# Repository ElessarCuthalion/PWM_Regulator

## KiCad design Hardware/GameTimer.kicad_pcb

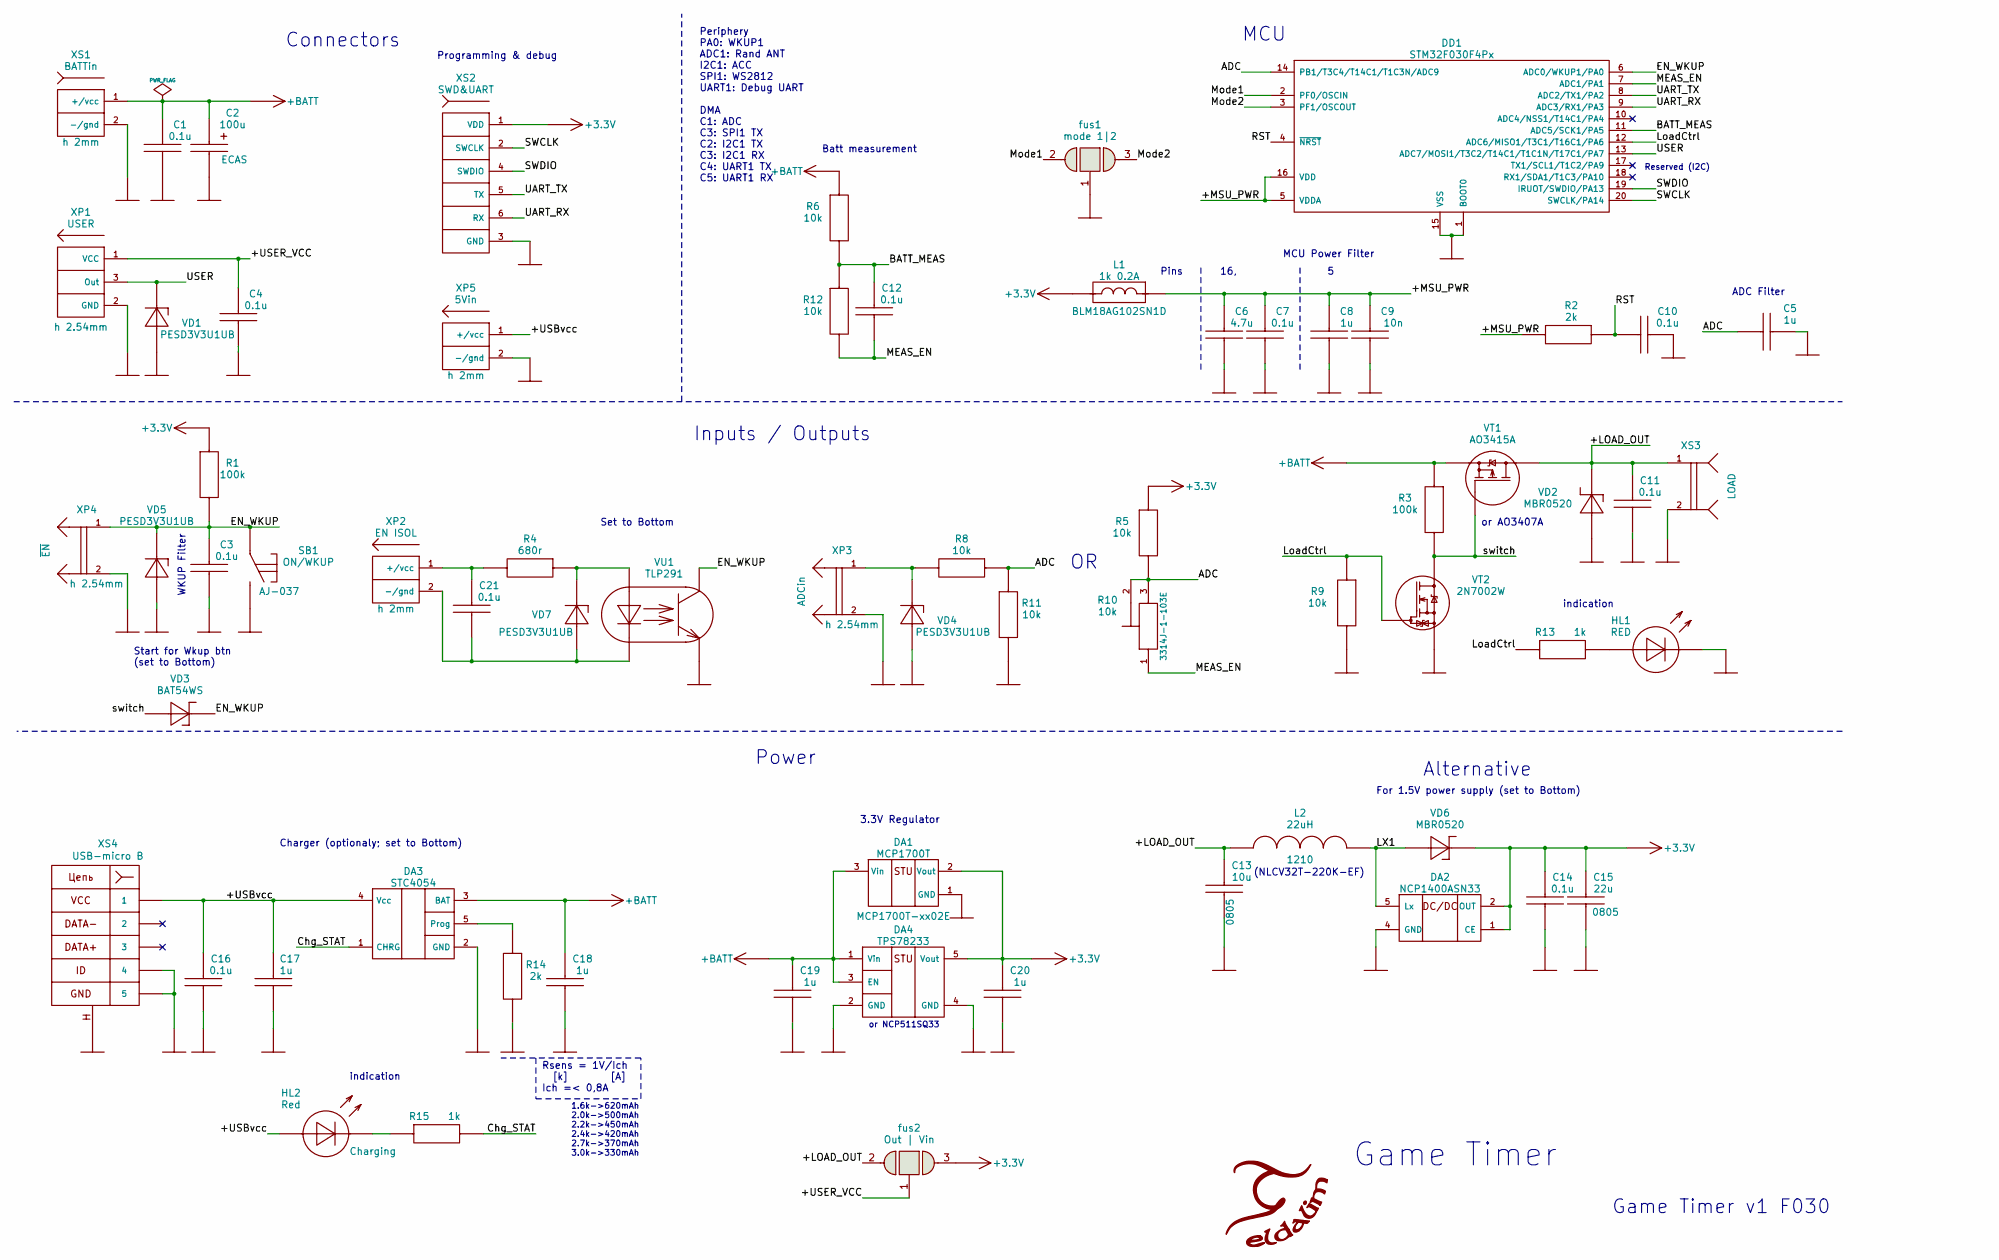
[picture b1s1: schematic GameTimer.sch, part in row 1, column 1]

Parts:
C1, C3, C4, C7, C10, C11, C12, C14, C16, C21: 0.1u; CAP0603
C2: 100u; CAP_pol_SMD-7343
C5, C8, C17, C18, C19, C20: 1u; CAP0603
C6: 4.7u; CAP0603
C9: 10n; CAP0603
C13: 10u; CAP0805
C15: 22u; CAP0805
DA1: MCP1700T; SOT23-3
DA2: NCP1400ASN33; SOT23-5
DA3: STC4054; SOT23-5
DA4: TPS78233; SOT23-5
DD1: STM32F030F4Px; TSSOP20
HL1: RED; LED0805
HL2: Red; LED0805
L1: 1k 0.2A; Bead_0603
L2: 22uH; IND1210_LQH32C
Logo1: Eldalim; Eldalim_10x8
R1, R3: 100k; RES0603
R2, R14: 2k; RES0603
R4: 680r; RES0603
R5, R6, R8, R9, R11, R12: 10k; RES0603
R10: 10k; RES_TRIM_Bourns3314J-1
R13, R15: 1k; RES0603
SB1: ON/WKUP; BTN_5x5(AJ-037)
VD1, VD4, VD5, VD7: PESD3V3U1UB; SOD523
VD2, VD6: MBR0520; SOD123
VD3: BAT54WS; SOD323
VT1: AO3415A; SOT23A
VT2: 2N7002W; SOT323
VU1: TLP291; opto_SOP4
XP1: USER; for_SENS_PLS2-3
XP2: EN ISOL; for_PolarOut_PLS2-2
XP3: ADCin; PLS2-2
XP4: ~EN; PLS2-2
XP5: 5Vin; for_PolarOut_PLS2-2
XS1: BATTin; for_PolarOut_PLS2-2
XS2: SWD&UART; for_SWD&UART_PBS-6
XS3: LOAD; PBS2-2
XS4: USB-micro B; USB-micro_B
fus1: mode 1|2; FuseSolder_x2_0603
fus2: Out | Vin; FuseSolder_x2_0603

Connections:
+3.3V: C14.1, C15.1, C20.1, DA1.2 (Vout), DA2.1 (CE), DA2.2 (OUT), DA4.5 (Vout), L1.1, R1.1, R5.1, VD6.C, XS2.1 (VDD), fus2.3
+BATT: C1.1, C2.1, C18.1, C19.1, DA1.3 (Vin), DA3.3 (BAT), DA4.1 (Vin), DA4.3 (EN), R3.1, R6.1, VT1.2 (S), XS1.1 (+/vcc)
/+LOAD_OUT: C11.1, C13.1, L2.1, VD2.C, VT1.3 (D), XS3.1, fus2.2
/+MSU_PWR: C6.1, C7.1, C8.1, C9.1, DD1.5 (VDDA), DD1.16 (VDD), L1.2, R2.2
/+USBvcc: C16.1, C17.1, DA3.4 (Vcc), HL2.A, XP5.1 (+/vcc), XS4.1
/+USER_VCC: C4.1, XP1.1 (VCC), fus2.1
/ADC: C5.1, DD1.14 (PB1/T3C4/T14C1/T1C3N/ADC9), R5.2, R8.1, R10.2, R10.3, R11.1
/BATT_MEAS: C12.1, DD1.11 (ADC5/SCK1/PA5), R6.2, R12.1
/Chg_STAT: DA3.1 (CHRG), R15.2
/EN_WKUP: C3.1, DD1.6 (ADC0/WKUP1/PA0), R1.2, SB1.1, VD3.C, VD5.C, VU1.4 (C), XP4.1
/LX1: DA2.5 (Lx), L2.2, VD6.A
/LoadCtrl: DD1.12 (ADC6/MISO1/T3C1/T16C1/PA6), R9.1, R13.1, VT2.1 (G)
/MEAS_EN: C12.2, DD1.7 (ADC1/PA1), R10.1, R12.2
/Mode1: DD1.2 (PF0/OSCIN), fus1.2
/Mode2: DD1.3 (PF1/OSCOUT), fus1.3
/RST: C10.1, DD1.4 (~NRST), R2.1
/SWCLK: DD1.20 (SWCLK/PA14), XS2.2 (SWCLK)
/SWDIO: DD1.19 (IRUOT/SWDIO/PA13), XS2.4 (SWDIO)
/UART_RX: DD1.9 (ADC3/RX1/PA3), XS2.6 (RX)
/UART_TX: DD1.8 (ADC2/TX1/PA2), XS2.5 (TX)
/USER: DD1.13 (ADC7/MOSI1/T3C2/T14C1/T1C1N/T17C1/PA7), VD1.C, XP1.3 (Out)
/switch: R3.2, VD3.A, VT1.1 (G), VT2.3 (D)
GND: C1.2, C2.2, C3.2, C4.2, C5.2, C6.2, C7.2, C8.2, C9.2, C10.2, C11.2, C13.2, C14.2, C15.2, C16.2, C17.2, C18.2, C19.2, C20.2, DA1.1 (GND), DA2.4 (GND), DA3.2 (GND), DA4.2 (GND), DA4.4 (GND), DD1.1 (BOOT0), DD1.15 (VSS), HL1.C, R9.2, R11.2, R14.2, SB1.2, VD1.A, VD2.A, VD4.A, VD5.A, VT2.2 (S), VU1.3 (E), XP1.2 (GND), XP3.2, XP4.2, XP5.2 (-/gnd), XS1.2 (-/gnd), XS2.3 (GND), XS3.2, XS4.4, XS4.5, XS4.SHLD, fus1.1
unnamed: C21.1, R4.2, XP2.1 (+/vcc)
unnamed: C21.2, VD7.A, VU1.2 (C), XP2.2 (-/gnd)
unnamed: DA3.5 (Prog), R14.1
unnamed: HL1.A, R13.2
unnamed: HL2.C, R15.1
unnamed: R4.1, VD7.C, VU1.1 (A)
unnamed: R8.2, VD4.C, XP3.1

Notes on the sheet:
Game Timer
Game Timer v1 F030
Programming & debug
Periphery PA0: WKUP1 ADC1: Rand ANT I2C1: ACC SPI1: WS2812 UART1: Debug UART DMA C1: ADC C3: SPI1 TX C2: I2C1 TX C3: I2C1 RX C4: UART1 TX C5: UART1 RX
MCU
Power
Connectors
MCU Power Filter
Pins 16, 5
indication
3.3V Regulator
Inputs / Outputs
WKUP Filter
ADC Filter
Reserved (I2C)
or AO3407A
or NCP511SQ33
Set to Bottom
Batt measurement
(NLCV32T-220K-EF)
For 1.5V power supply (set to Bottom)
Alternative
Rsens = 1V/Ich [k] [A] Ich =< 0,8A
1.6k->620mAh 2.0k->500mAh 2.2k->450mAh 2.4k->420mAh 2.7k->370mAh 3.0k->330mAh
Charger (optionaly; set to Bottom)
Start for Wkup btn (set to Bottom)

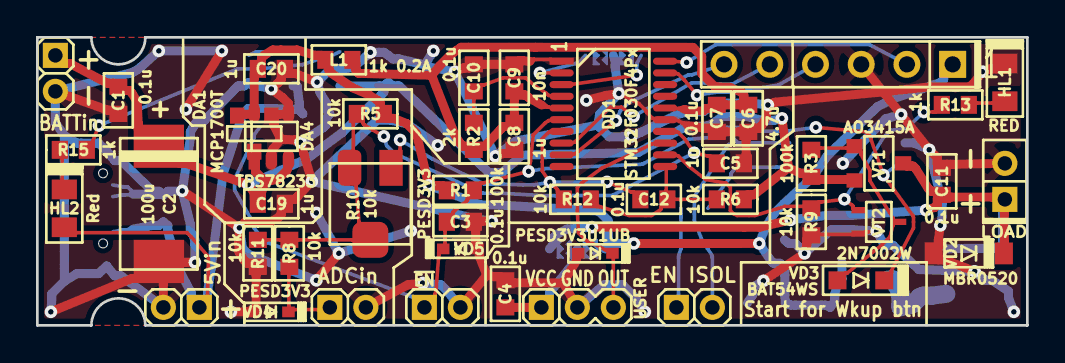
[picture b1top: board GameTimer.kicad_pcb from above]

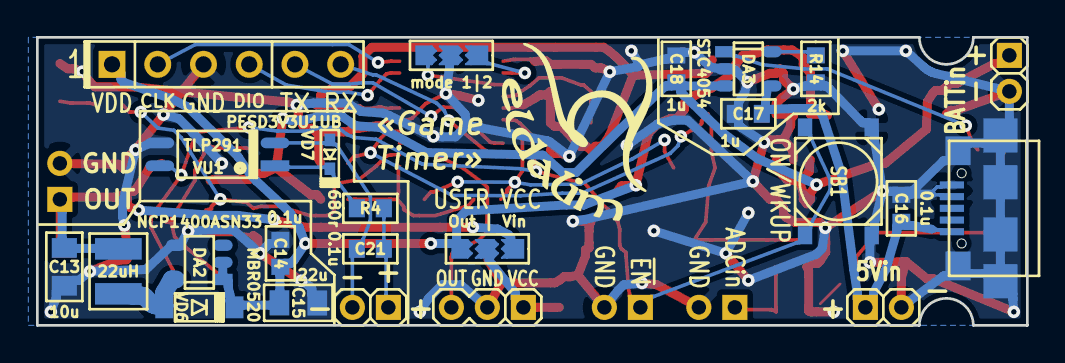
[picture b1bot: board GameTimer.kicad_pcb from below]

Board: 2 copper layers, 55.0 x 16.0 mm, 67 parts (20 on the bottom side), 30 nets.

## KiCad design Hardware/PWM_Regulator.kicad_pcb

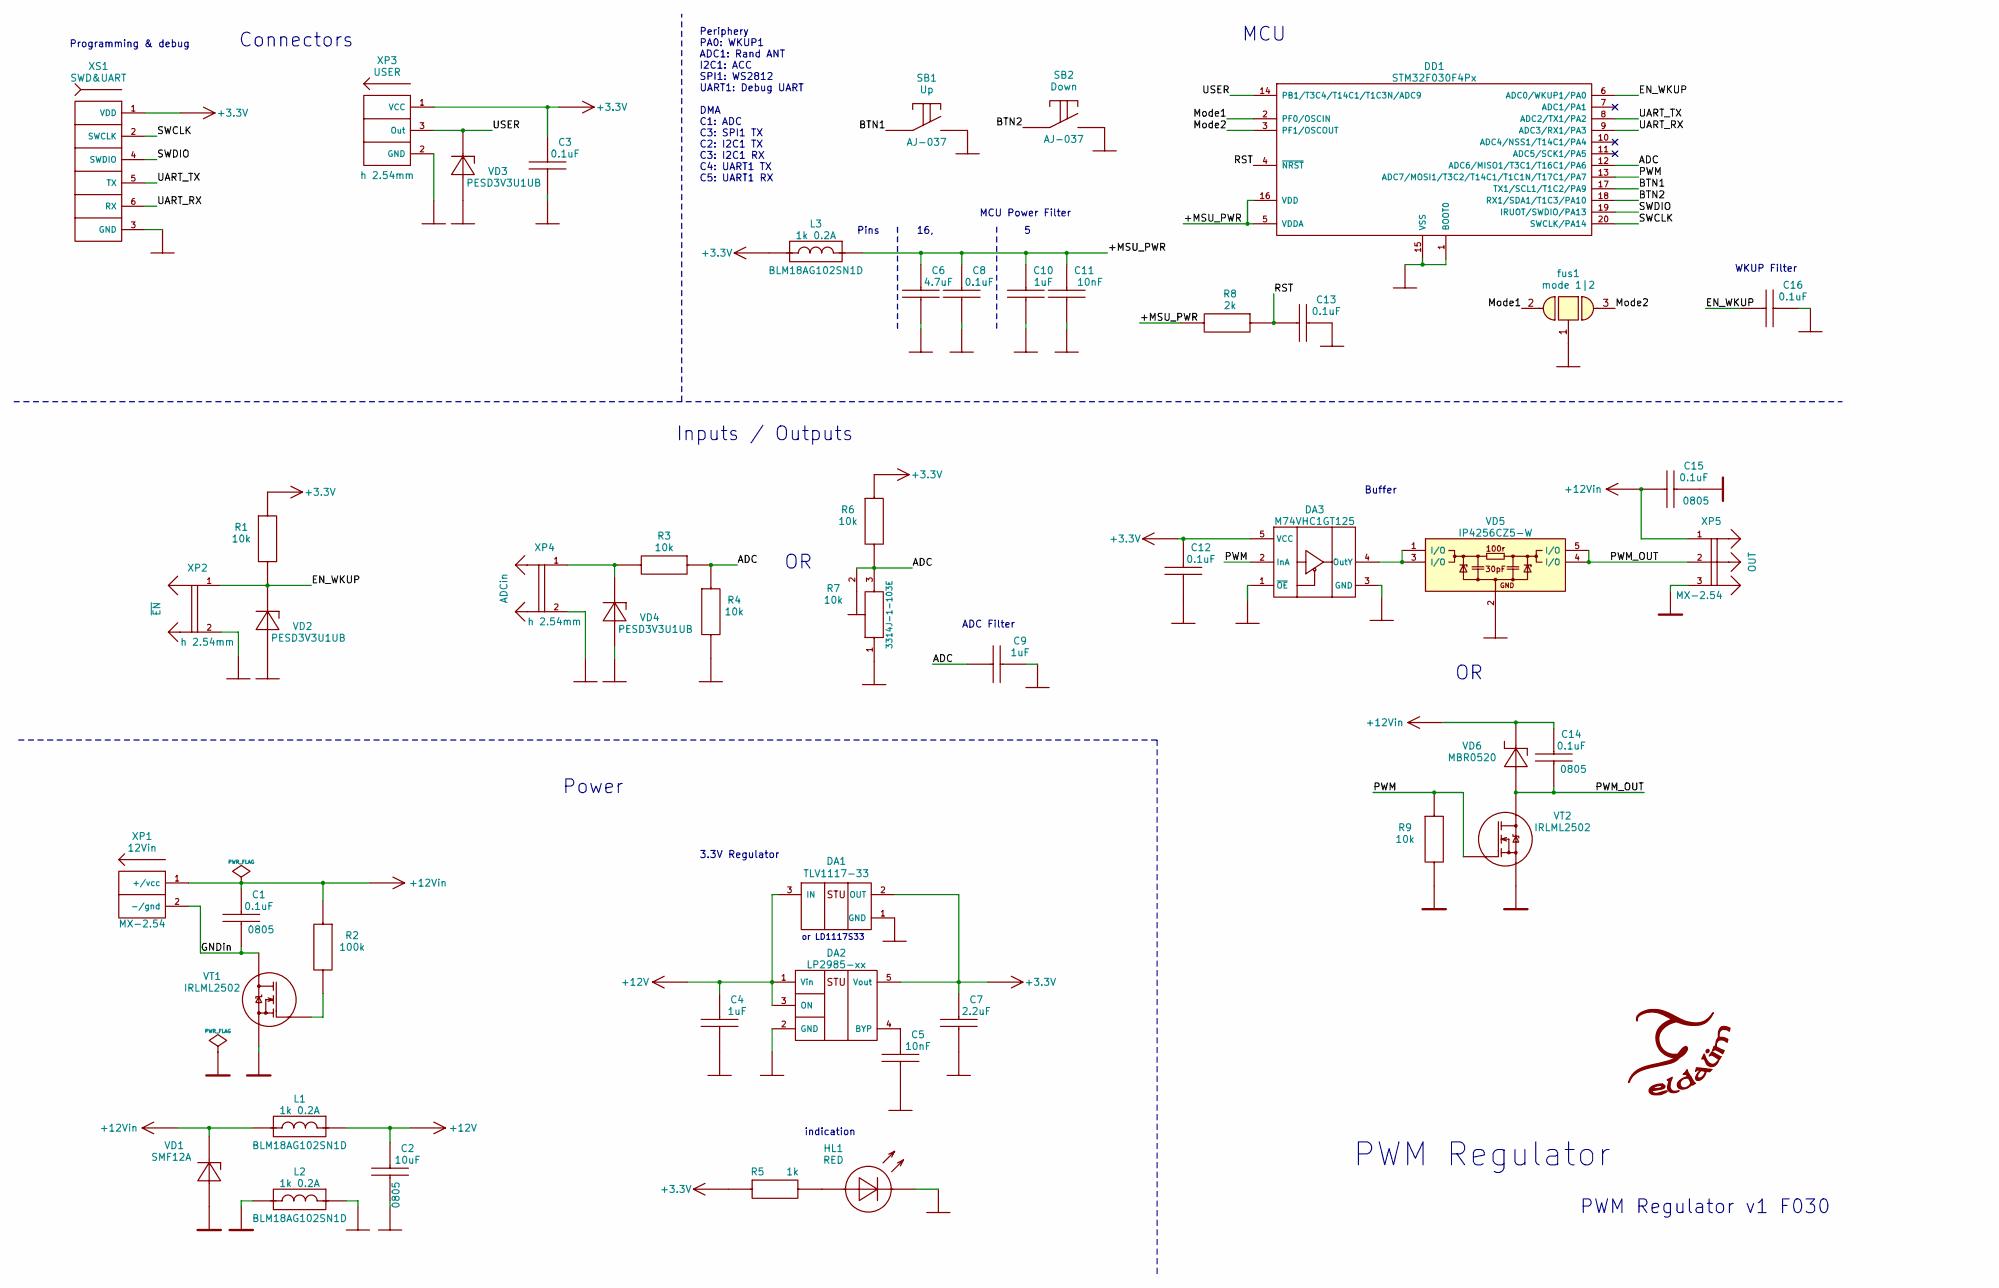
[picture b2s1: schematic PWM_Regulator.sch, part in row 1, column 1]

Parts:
C1, C14, C15: 0.1uF; CAP0805
C2: 10uF; CAP0805
C3, C8, C12, C13, C16: 0.1uF; CAP0603
C4, C9, C10: 1uF; CAP0603
C5, C11: 10nF; CAP0603
C6: 4.7uF; CAP0603
C7: 2.2uF; CAP0603
DA1: TLV1117-33; SOT223
DA2: LP2985-xx; SOT23-5
DA3: M74VHC1GT125; SOT23-5
DD1: STM32F030F4Px; TSSOP20
HL1: RED; LED0805
L1, L2, L3: 1k 0.2A; Bead_0603
Logo1: Eldalim; Eldalim_10x8
R1, R3, R4, R6, R9: 10k; RES0603
R2: 100k; RES0603
R5: 1k; RES0603
R7: 10k; RES_TRIM_Bourns3314J-1
R8: 2k; RES0603
SB1: Up; BTN_5x5(AJ-037)
SB2: Down; BTN_5x5(AJ-037)
VD1: SMF12A; SOD123
VD2, VD3, VD4: PESD3V3U1UB; SOD523
VD5: IP4256CZ5-W; SOT665
VD6: MBR0520; SOD123
VT1, VT2: IRLML2502; SOT23-3
XP1: 12Vin; for_PolarOut_MX2.54-2R
XP2: ~EN; PLS-2
XP3: USER; for_SENS_PLS-3
XP4: ADCin; PLS-2
XP5: OUT; MX2.54-3R
XS1: SWD&UART; for_SWD&UART_PBS-6
fus1: mode 1|2; FuseSolder_x2_0603

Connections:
+3.3V: C3.1, C7.1, C12.1, DA1.2 (OUT), DA2.5 (Vout), DA3.5 (VCC), L3.1, R1.1, R5.1, R6.1, XP3.1 (VCC), XS1.1 (VDD)
+12V: C2.1, C4.1, DA1.3 (IN), DA2.1 (Vin), DA2.3 (ON), L1.2
+12Vin: C1.1, C14.1, C15.1, L1.1, R2.1, VD1.C, VD6.C, XP1.1 (+/vcc), XP5.1
/+MSU_PWR: C6.1, C8.1, C10.1, C11.1, DD1.5 (VDDA), DD1.16 (VDD), L3.2, R8.2
/ADC: C9.1, DD1.12 (ADC6/MISO1/T3C1/T16C1/PA6), R3.1, R4.1, R6.2, R7.2, R7.3
/BTN1: DD1.17 (TX1/SCL1/T1C2/PA9), SB1.1
/BTN2: DD1.18 (RX1/SDA1/T1C3/PA10), SB2.1
/EN_WKUP: C16.1, DD1.6 (ADC0/WKUP1/PA0), R1.2, VD2.C, XP2.1
/GNDin: C1.2, VT1.3 (D), XP1.2 (-/gnd)
/Mode1: DD1.2 (PF0/OSCIN), fus1.2
/Mode2: DD1.3 (PF1/OSCOUT), fus1.3
/PWM: DA3.2 (InA), DD1.13 (ADC7/MOSI1/T3C2/T14C1/T1C1N/T17C1/PA7), R9.1, VT2.1 (G)
/PWM_OUT: C14.2, VD5.4 (I/O), VD5.5 (I/O), VD6.A, VT2.3 (D), XP5.2
/RST: C13.1, DD1.4 (~NRST), R8.1
/SWCLK: DD1.20 (SWCLK/PA14), XS1.2 (SWCLK)
/SWDIO: DD1.19 (IRUOT/SWDIO/PA13), XS1.4 (SWDIO)
/UART_RX: DD1.9 (ADC3/RX1/PA3), XS1.6 (RX)
/UART_TX: DD1.8 (ADC2/TX1/PA2), XS1.5 (TX)
/USER: DD1.14 (PB1/T3C4/T14C1/T1C3N/ADC9), VD3.C, XP3.3 (Out)
GND: C2.2, C3.2, C4.2, C5.2, C6.2, C7.2, C8.2, C9.2, C10.2, C11.2, C12.2, C13.2, C16.2, DA1.1 (GND), DA2.2 (GND), DA3.1 (~OE), DA3.3 (GND), DD1.1 (BOOT0), DD1.15 (VSS), HL1.C, L2.2, R4.2, R7.1, SB1.2, SB2.2, VD2.A, VD3.A, VD4.A, VD5.2, XP2.2, XP3.2 (GND), XP4.2, XS1.3 (GND), fus1.1
GNDP: C15.2, L2.1, R9.2, VD1.A, VT1.2 (S), VT2.2 (S), XP5.3
unnamed: C5.1, DA2.4 (BYP)
unnamed: DA3.4 (OutY), VD5.1 (I/O), VD5.3 (I/O)
unnamed: HL1.A, R5.2
unnamed: R2.2, VT1.1 (G)
unnamed: R3.2, VD4.C, XP4.1

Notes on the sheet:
PWM Regulator
PWM Regulator v1 F030
Programming & debug
Periphery PA0: WKUP1 ADC1: Rand ANT I2C1: ACC SPI1: WS2812 UART1: Debug UART DMA C1: ADC C3: SPI1 TX C2: I2C1 TX C3: I2C1 RX C4: UART1 TX C5: UART1 RX
MCU
Power
Connectors
MCU Power Filter
Pins 16, 5
indication
3.3V Regulator
or LD1117S33
Inputs / Outputs
Buffer
WKUP Filter
ADC Filter

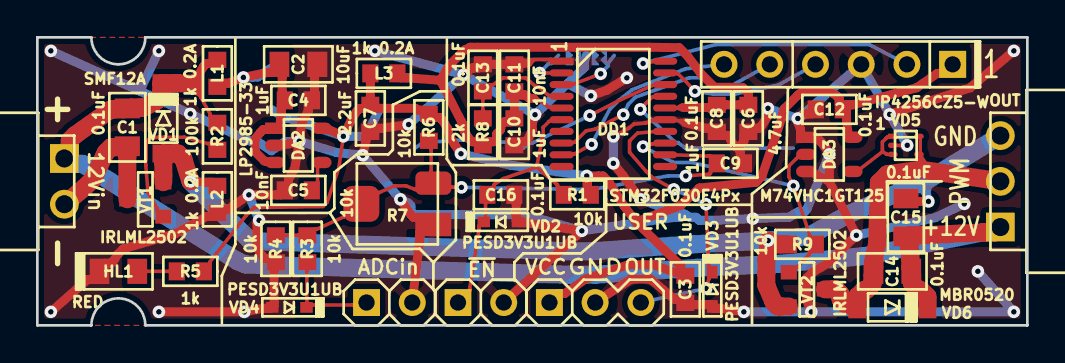
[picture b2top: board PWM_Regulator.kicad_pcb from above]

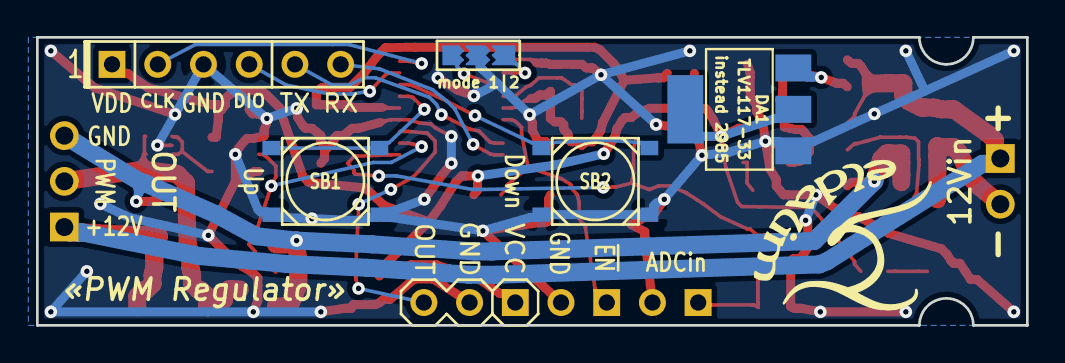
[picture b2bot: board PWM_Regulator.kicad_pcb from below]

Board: 2 copper layers, 55.0 x 16.0 mm, 51 parts (5 on the bottom side), 26 nets.

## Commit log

2019-10-15 Firmware в первом приближении...
2019-10-16 настройка
2019-10-25 fix Buttons
2019-10-30 F030 fix
2020-11-02 + Hardware; подготовка к трассировке
2020-11-02 Разводка проводников на плате PWM_Regulator
2020-11-03 Трассировка завершена.
2020-11-03 Доделано заземление, расставлены надписи
2020-11-04 работа завершена
2022-05-11 преход на кодировку UTF-8
2022-07-10 заметки
2022-07-12 Таймер для игрушек: примерная схема
2022-07-22 комментарии
2022-08-15 Игровой таймер: расстановка компонентов наяата
2022-09-14 Игровой таймер: компоненты расставлены
2022-09-22 GameTimer: работа завершена
